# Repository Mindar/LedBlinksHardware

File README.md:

# LedBlinks
LedBlinks is a wifi configurable controller/driver for up to 3 independent channels. It can be used to control RGB LED strips over wifi. But you can control any other load, for example three independent white led strips or just 3 single leds.

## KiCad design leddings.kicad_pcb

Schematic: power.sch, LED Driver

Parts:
C1, C2: 10uF; C_0805_HandSoldering
D1: D; D_0805
D2: LED; LED_0805_HandSoldering
J6: Barrel_Jack; Barrel_Jack_CUI_PJ-102AH
MK1, MK2, MK3, MK4: Mounting_Hole; MountingHole_3.2mm_M3_DIN965_Pad
R9: 1K; R_0805_HandSoldering
U1: LM1117-3.3; TO-220-3_Vertical

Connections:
+12V: C1.1, D1.1, J6.1, U1.3; also elsewhere on the board
GND: C1.2, C2.2, D2.1 (K), J6.2, J6.3, U1.1; also elsewhere on the board
unnamed: D2.2 (A), R9.2
VBUS: D1.2; also elsewhere on the board
VCC: C2.1, R9.1, U1.2; also elsewhere on the board

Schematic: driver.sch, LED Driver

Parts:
J1, J2, J3: TEST_1P; Measurement_Point_Square-SMD-Pad_Small
J4: Conn_01x04; Pin_Header_Straight_1x04_Pitch2.54mm
Q1, Q2, Q3: FQP30N06L; TO-220-3_Vertical
R1, R2, R3: 100R; R_0805_HandSoldering
R4, R5, R6: 10K; R_0805_HandSoldering

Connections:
+12V: J4.1; also elsewhere on the board
/Controller/BLUE: R2.2; also elsewhere on the board
/Controller/GREEN: R3.2; also elsewhere on the board
/Controller/RED: R1.2; also elsewhere on the board
/LED Driver/BlueChannel: J4.3, Q2.2; also elsewhere on the board
/LED Driver/GreenChannel: J4.2, Q3.2; also elsewhere on the board
/LED Driver/RedChannel: J4.4, Q1.2; also elsewhere on the board
GND: Q1.3, Q2.3, Q3.3, R4.2, R5.2, R6.2; also elsewhere on the board
unnamed: Q1.1, R1.1, R4.1
unnamed: Q2.1, R2.1, R5.1
unnamed: Q3.1, R3.1, R6.1

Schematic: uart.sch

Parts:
C3, C4: 22pF; C_0805_HandSoldering
J5: Micro USB; USB_Micro-B_Molex-105017-0001
U2: CH340G; SOIC-16_3.9x9.9mm_Pitch1.27mm
Y1: 12 Mhz Crystal; Crystal_HC49-U_Vertical

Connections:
/Controller/BOOT_SELECT: U2.13 (DTR); also elsewhere on the board
/Controller/RESET: U2.14 (RTS); also elsewhere on the board
/Controller/RX: U2.2 (TX); also elsewhere on the board
/USB UART Interface/RX: U2.3 (RX); also elsewhere on the board
GND: C3.2, C4.2, J5.4, J5.5, J5.6, U2.1 (GND); also elsewhere on the board
unnamed: C3.1, U2.7 (XI), Y1.1
unnamed: C4.1, U2.8 (XO), Y1.2
unnamed: J5.2, U2.6 (D-)
unnamed: J5.3, U2.5 (D+)
VBUS: J5.1; also elsewhere on the board
VCC: U2.4 (V3), U2.16 (VCC); also elsewhere on the board

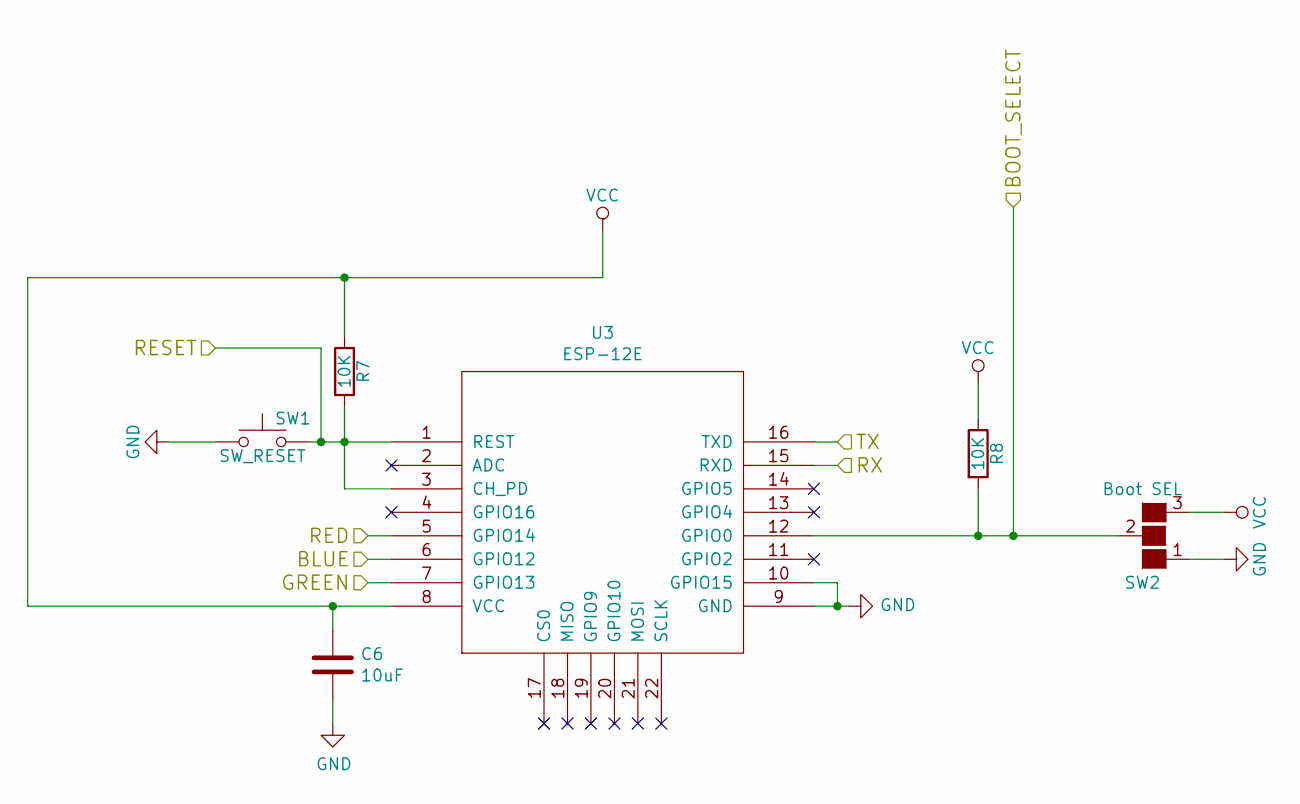
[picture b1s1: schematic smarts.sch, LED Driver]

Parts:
C6: 10uF; R_0805_2012Metric_Pad1.15x1.40mm_HandSolder
R7, R8: 10K; R_0805_HandSoldering
SW1: SW_RESET; SW_SPST_B3S-1000
SW2: Boot SEL; Pin_Header_Straight_1x03_Pitch2.54mm
U3: ESP-12E; ESP-12E_SMD

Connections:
/Controller/BLUE: U3.6 (GPIO12); also elsewhere on the board
/Controller/BOOT_SELECT: R8.2, SW2.2 (G2), U3.12 (GPIO0); also elsewhere on the board
/Controller/GREEN: U3.7 (GPIO13); also elsewhere on the board
/Controller/RED: U3.5 (GPIO14); also elsewhere on the board
/Controller/RESET: R7.2, SW1.2, U3.1 (REST), U3.3 (CH_PD); also elsewhere on the board
/Controller/RX: U3.15 (RXD); also elsewhere on the board
/USB UART Interface/RX: U3.16 (TXD); also elsewhere on the board
GND: C6.2, SW1.1, SW2.1 (G1), U3.9 (GND), U3.10 (GPIO15); also elsewhere on the board
VCC: C6.1, R7.1, R8.1, SW2.3 (G3), U3.8 (VCC); also elsewhere on the board

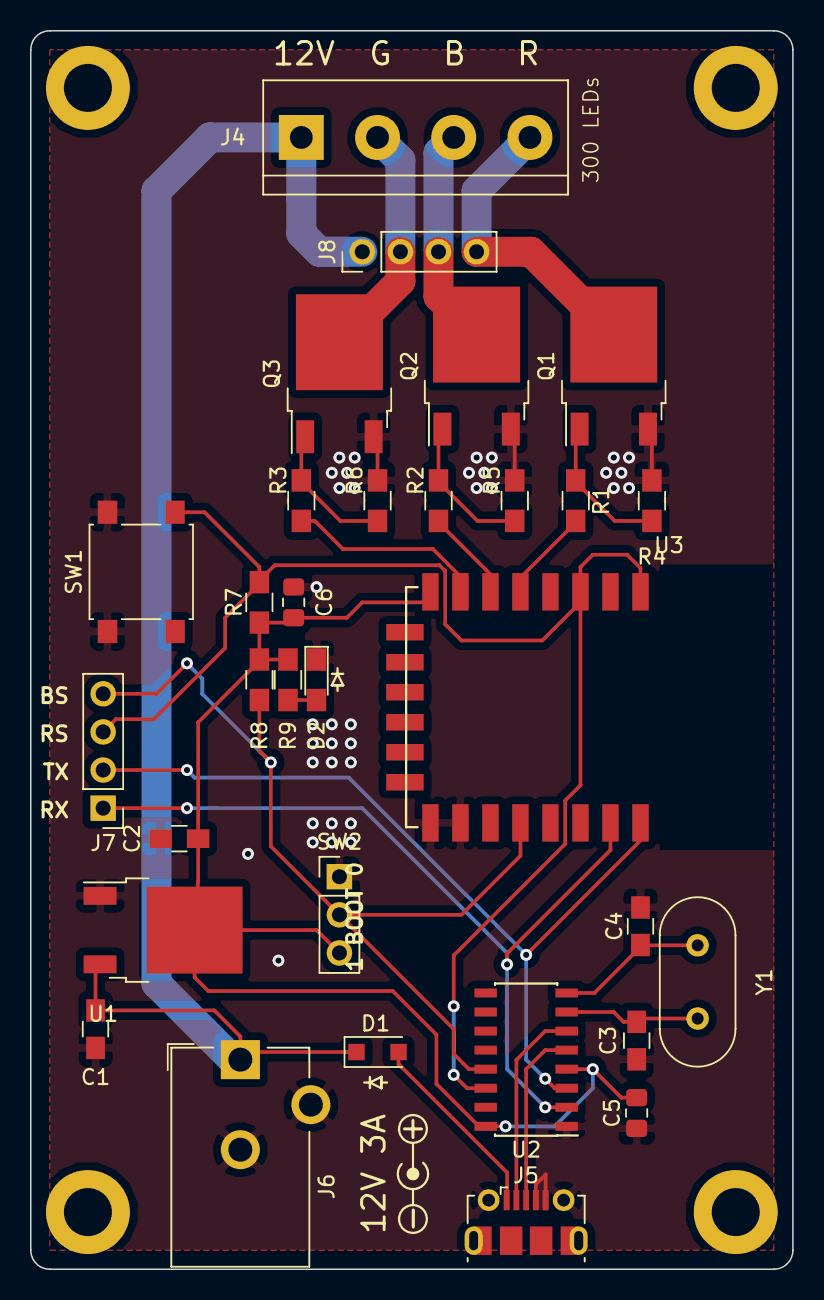
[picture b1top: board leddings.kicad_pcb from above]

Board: 2 copper layers, 50.8 x 82.6 mm, 35 parts (0 on the bottom side), 22 nets.

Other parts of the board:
C5: 10uF; C_0805_2012Metric_Pad1.15x1.40mm_HandSolder
J7: Conn_01x04; Pin_Header_Straight_1x04_Pitch2.54mm
J8: Conn_01x04; PinHeader_1x04_P2.54mm_Vertical

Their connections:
+12V: J8.1; also elsewhere on the board
/Controller/BOOT_SELECT: J7.4; also elsewhere on the board
/Controller/RESET: J7.3; also elsewhere on the board
/Controller/RX: J7.1; also elsewhere on the board
/LED Driver/BlueChannel: J8.3; also elsewhere on the board
/LED Driver/GreenChannel: J8.2; also elsewhere on the board
/LED Driver/RedChannel: J8.4; also elsewhere on the board
/USB UART Interface/RX: J7.2; also elsewhere on the board
GND: C5.1; also elsewhere on the board
VCC: C5.2; also elsewhere on the board

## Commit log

2018-06-07 added stuff
2018-08-01 Did a stuff
2018-08-01 added pics
2018-10-02 added pin headers for uart, added power-on-led, improved routing
2018-11-23 changed some parts to smd, fixed some design errors
2018-11-28 changed text on pcb
